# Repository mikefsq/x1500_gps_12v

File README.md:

# x1500_gps_12v

KiCad project for a daughterboard that powers a [Geekworm X1500](https://geekworm.com/products/x1500) (Raspberry Pi CM5,
1GbE, Dual M.2 NVMe SSD). It powers the Pi from 12V and adds a NEO-M9N GPS receiver 
with PPS, an SHT45 humidity sensor and a BMP581 pressure sensor. Also has a u.fl to SMA
jumper to help with attaching a WiFi Antenna.

Note this PCB does not cover the CM5 and its heat sink. If using another Pi board 
remember that it does not stack like a regular pi-hat.

## Driver software

The [Go GPS/weather library and diagnostic tools](driver/README.md) are in
`driver/`. They run on the Raspberry Pi and are licensed under AGPL-3.0-only.

## Raspberry Pi setup

```sh
sudo apt install gpsd gpsd-clients chrony pps-tools i2c-tools
```

Add to `/boot/firmware/config.txt`:

```
[all]
dtparam=i2c_arm=on
dtparam=uart0=on
dtoverlay=pps-gpio,gpiopin=18
usb_max_current_enable=1
dtparam=pciex1
```

Add to `/etc/default/gpsd`:

```
DEVICES="/dev/ttyAMA0"
GPSD_OPTIONS="-n -s 38400"
USBAUTO="false"
```

Add to `/etc/chrony/conf.d/gps.conf`:

```
refclock SHM 0 refid NMEA offset 0.0 precision 1e-1 noselect
refclock PPS /dev/pps0 refid PPS lock NMEA precision 1e-7 prefer
allow 192.168.0.0/24
```

Add to `/etc/systemd/system/gpsd.socket.d/90-network.conf`:

```
[Socket]
ListenStream=
ListenStream=/run/gpsd.sock
ListenStream=0.0.0.0:2947
```

Enable I2C `/etc/modules-load.d/i2c.conf`:

```
i2c-dev
```

```sh
sudo systemctl daemon-reload
sudo systemctl enable gpsd.socket
sudo reboot
```

`chronyc sources -v` shows PPS selected once the receiver has a fix.

## License

Hardware: [CERN-OHL-S-2.0](LICENSE).

Driver software: [AGPL-3.0-only](driver/LICENSE).

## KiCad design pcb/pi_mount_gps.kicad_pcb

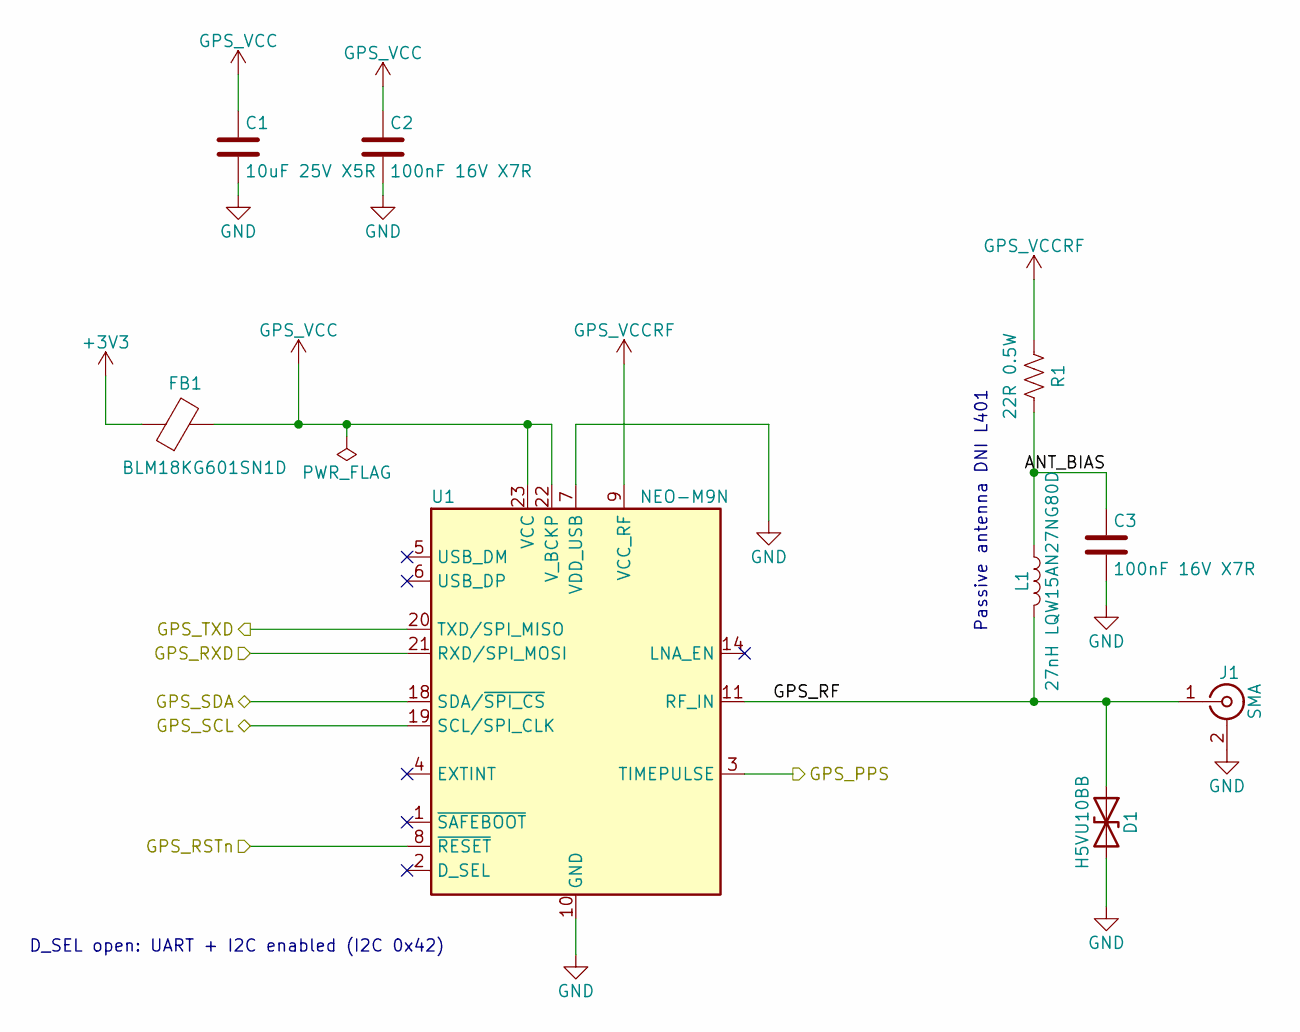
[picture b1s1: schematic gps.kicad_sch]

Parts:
C1: 10uF 25V X5R; C_0805_2012Metric; LCSC C15850
C2, C3: 100nF 16V X7R; C_0402_1005Metric; LCSC C1525
D1: H5VU10BB; D_0402_1005Metric; LCSC C20615786
FB1: BLM18KG601SN1D; L_0603_1608Metric; LCSC C85833
J1: SMA; SMA_Molex_73251-1153_EdgeMount_Horizontal
L1: 27nH LQW15AN27NG80D; L_0402_1005Metric; LCSC C882469
R1: 22R 0.5W; R_1206_3216Metric; LCSC C2845146
U1: NEO-M9N; ublox_NEO; LCSC C5119087

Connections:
+3V3: FB1.1; also elsewhere on the board
/GPS/ANT_BIAS: C3.1, L1.1, R1.2
/GPS/GPS_RF: D1.1 (A1), J1.1 (In), L1.2, U1.11 (RF_IN)
/GPS_PPS: U1.3 (TIMEPULSE); also elsewhere on the board
/GPS_RSTn: U1.8 (~RESET); also elsewhere on the board
/GPS_RXD: U1.21 (RXD/SPI_MOSI); also elsewhere on the board
/GPS_TXD: U1.20 (TXD/SPI_MISO); also elsewhere on the board
/I2C1_SCL: U1.19 (SCL/SPI_CLK); also elsewhere on the board
/I2C1_SDA: U1.18 (SDA/~SPI_CS); also elsewhere on the board
GND: C1.2, C2.2, C3.2, D1.2 (A2), J1.2 (Ext), U1.7 (VDD_USB), U1.10 (GND), U1.12 (GND), U1.13 (GND), U1.24 (GND); also elsewhere on the board
GPS_VCC: C1.1, C2.1, FB1.2, U1.22 (V_BCKP), U1.23 (VCC)
GPS_VCCRF: R1.1, U1.9 (VCC_RF)

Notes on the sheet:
D_SEL open: UART + I2C enabled (I2C 0x42)
Passive antenna DNI L401

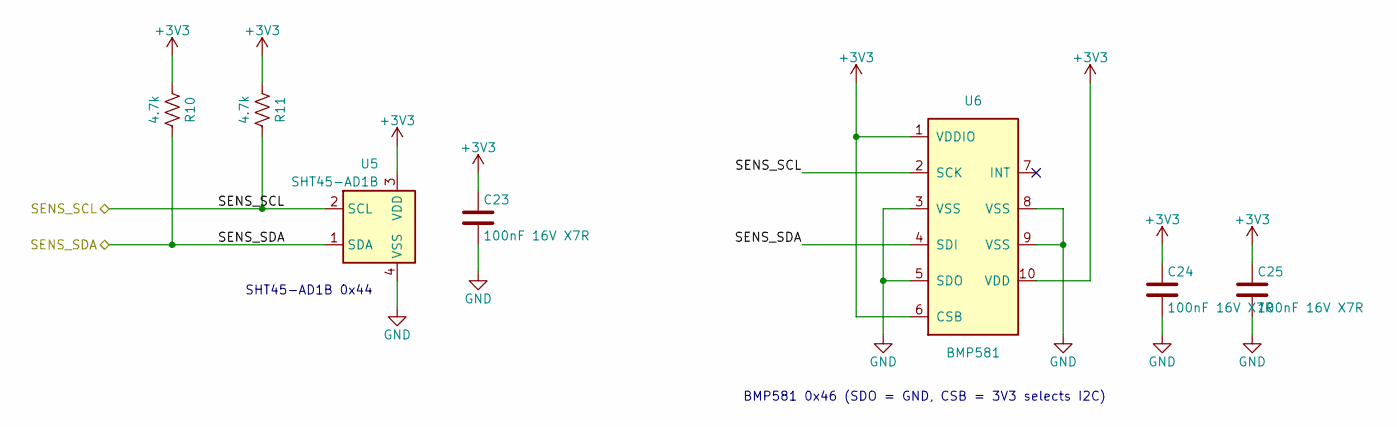
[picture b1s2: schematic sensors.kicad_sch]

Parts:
C23, C24, C25: 100nF 16V X7R; C_0402_1005Metric; LCSC C1525
R10, R11: 4.7k; R_0402_1005Metric; LCSC C25900
U5: SHT45-AD1B; Sensirion_DFN-4_1.5x1.5mm_P0.8mm_SHT4x_NoCentralPad; LCSC C5221601
U6: BMP581; Bosch_LGA-10_2x2mm_P0.5mm_BMP581; LCSC C5362283

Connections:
+3V3: C23.1, C24.1, C25.1, R10.1, R11.1, U5.3 (VDD), U6.1 (VDDIO), U6.6 (CSB), U6.10 (VDD); also elsewhere on the board
/I2C1_SCL: R11.2, U5.2 (SCL), U6.2 (SCK); also elsewhere on the board
/I2C1_SDA: R10.2, U5.1 (SDA), U6.4 (SDI); also elsewhere on the board
GND: C23.2, C24.2, C25.2, U5.4 (VSS), U6.3 (VSS), U6.5 (SDO), U6.8 (VSS), U6.9 (VSS); also elsewhere on the board

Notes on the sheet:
BMP581 0x46 (SDO = GND, CSB = 3V3 selects I2C)
SHT45-AD1B 0x44

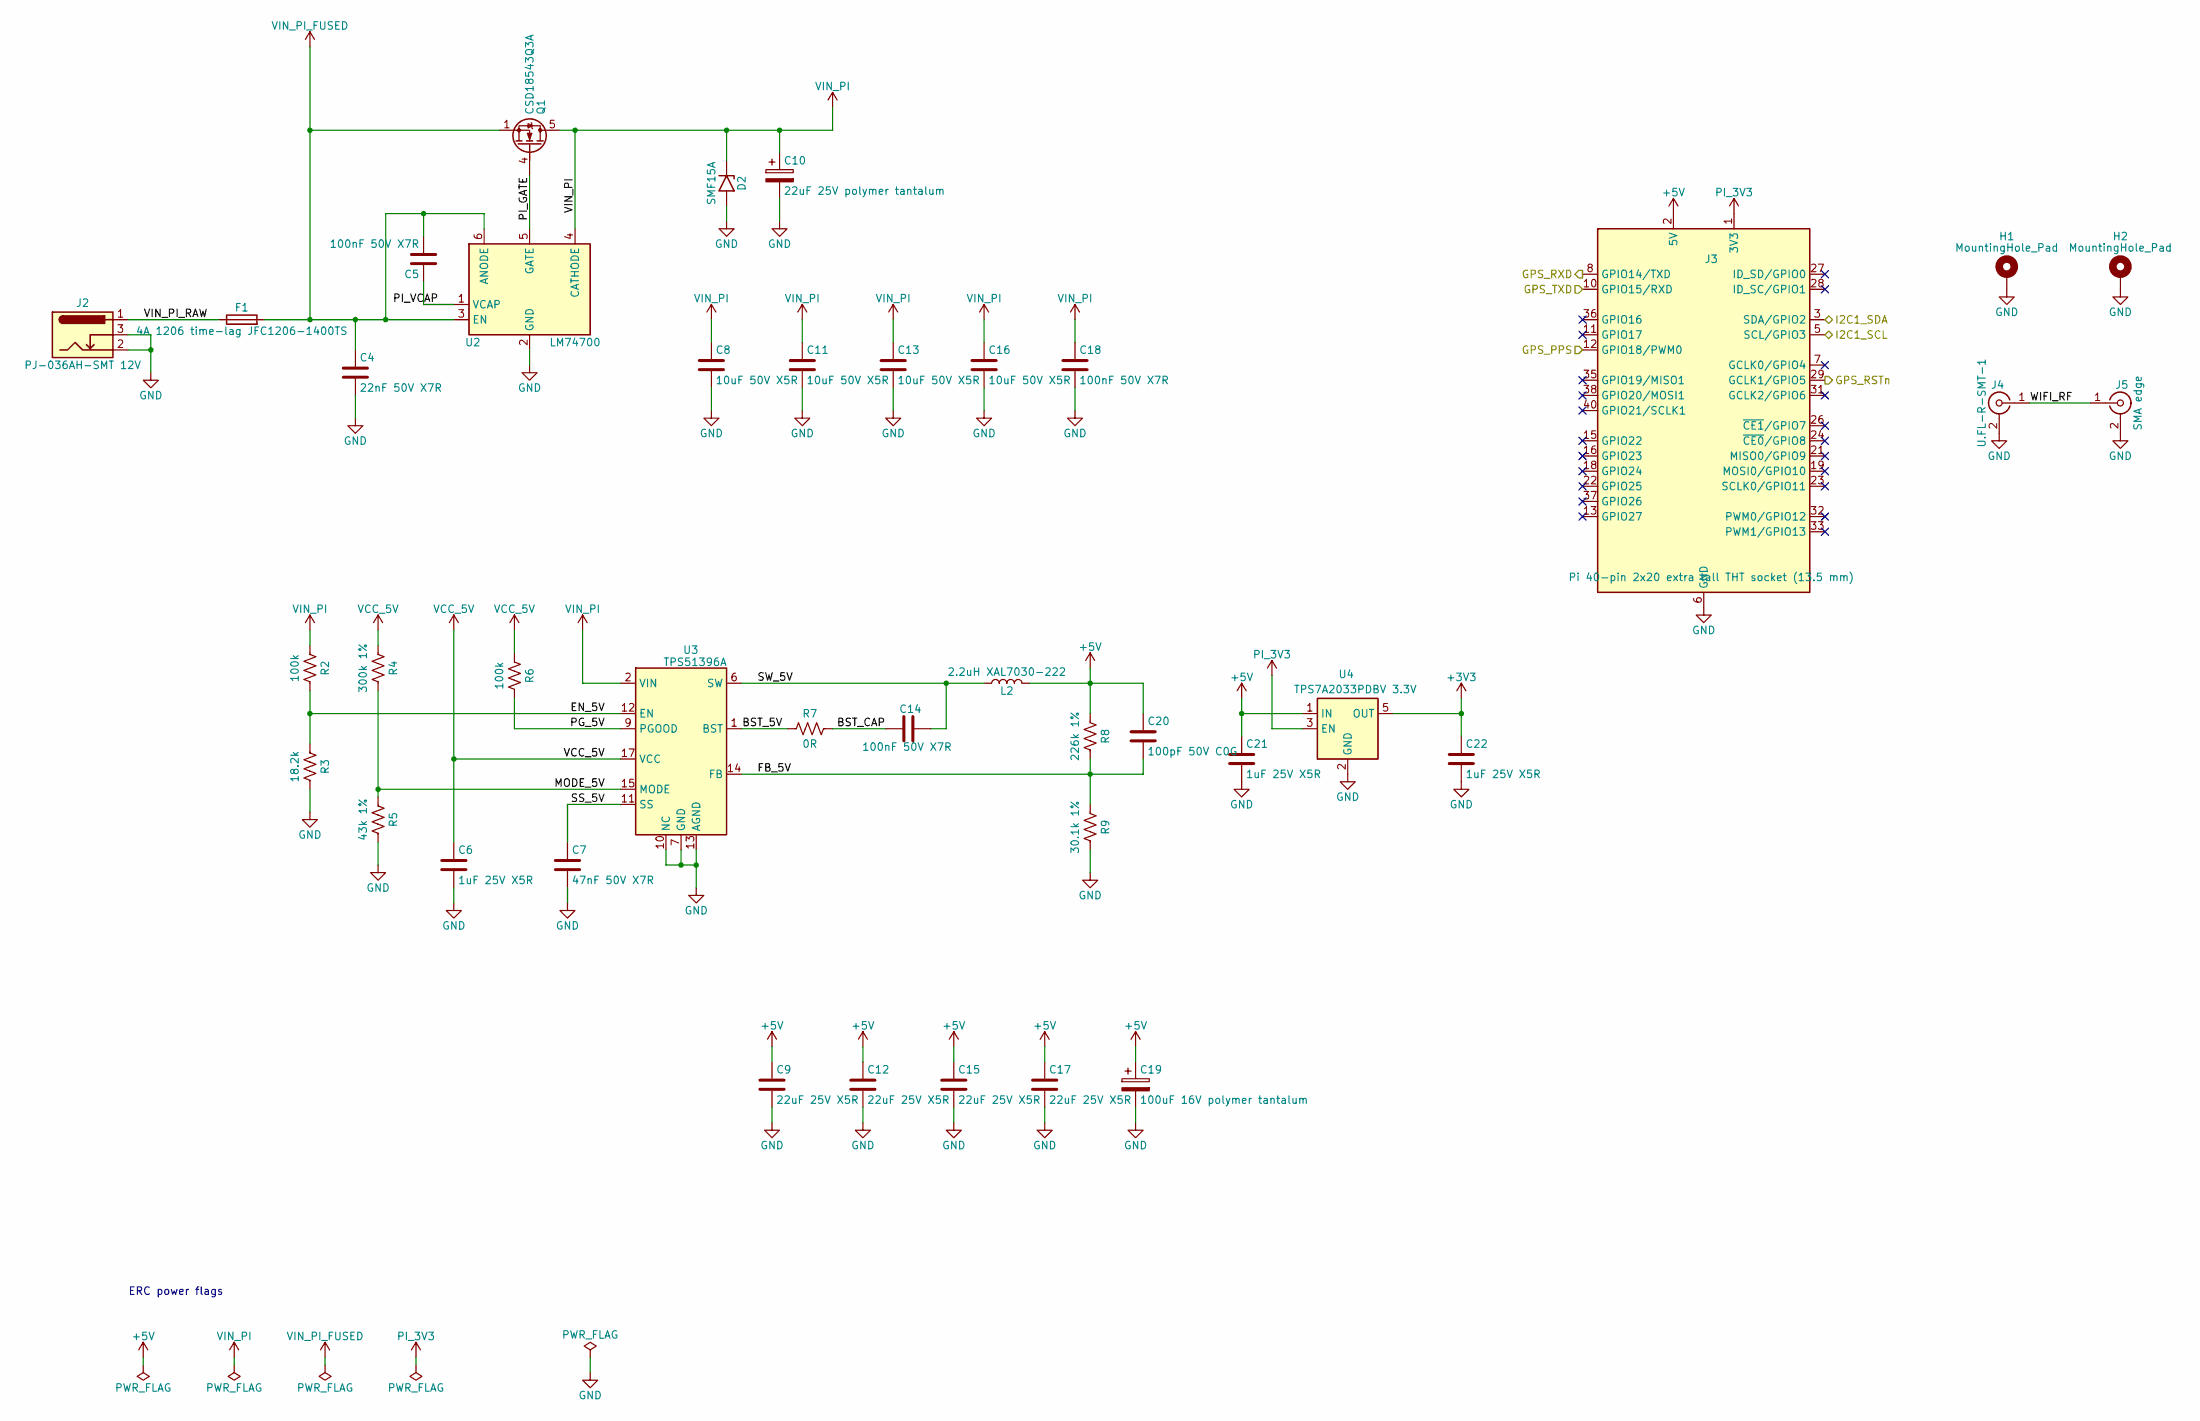
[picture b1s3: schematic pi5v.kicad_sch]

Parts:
C4: 22nF 50V X7R; C_0402_1005Metric; LCSC C1532
C5, C14, C18: 100nF 50V X7R; C_0402_1005Metric; LCSC C307331
C6, C21, C22: 1uF 25V X5R; C_0402_1005Metric; LCSC C52923
C7: 47nF 50V X7R; C_0402_1005Metric; LCSC C880605
C8, C11, C13, C16: 10uF 50V X5R; C_0805_2012Metric; LCSC C440198
C9, C12, C15, C17: 22uF 25V X5R; C_1206_3216Metric; LCSC C12891
C10: 22uF 25V polymer tantalum; CP_EIA-3528-21_Kemet-B; LCSC C696813
C19: 100uF 16V polymer tantalum; CP_EIA-7343-31_Kemet-D; LCSC C212713
C20: 100pF 50V C0G; C_0402_1005Metric; LCSC C1546
D2: SMF15A; D_SOD-123F; LCSC C19077509
F1: 4A 1206 time-lag JFC1206-1400TS; Fuse_1206_3216Metric; LCSC C52204055
H1, H2: MountingHole_Pad; MountingHole_2.7mm_M2.5_Pad_Via
J2: PJ-036AH-SMT 12V; BarrelJack_SameSky_PJ-036AH-SMT_Horizontal
J3: Pi 40-pin 2x20 extra tall THT socket (13.5 mm); PinSocket_2x20_P2.54mm_Vertical
J4: U.FL-R-SMT-1; U.FL_Hirose_U.FL-R-SMT-1_Vertical; LCSC C88374
J5: SMA edge; SMA_Molex_73251-1153_EdgeMount_Horizontal
L2: 2.2uH XAL7030-222; L_Coilcraft_XAL7030-222; LCSC C19191686
Q1: CSD18543Q3A; VSON-8_3.3x3.3mm_P0.65mm_NexFET; LCSC C840100
R2, R6: 100k; R_0402_1005Metric; LCSC C25741
R3: 18.2k; R_0402_1005Metric; LCSC C2998079
R4: 300k 1%; R_0402_1005Metric; LCSC C25774
R5: 43k 1%; R_0402_1005Metric; LCSC C54920674
R7: 0R; R_0402_1005Metric; LCSC C17168
R8: 226k 1%; R_0402_1005Metric; LCSC C5121518
R9: 30.1k 1%; R_0402_1005Metric; LCSC C2998131
U2: LM74700; SOT-23-6; LCSC C2653623
U3: TPS51396A; Texas_RJE0020A_VQFN-20-1EP_3x3mm_P0.45mm_EP0.675x0.76mm; LCSC C3032872
U4: TPS7A2033PDBV 3.3V; SOT-23-5; LCSC C2862740

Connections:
+3V3: C22.1, U4.5 (OUT); also elsewhere on the board
+5V: C9.1, C12.1, C15.1, C17.1, C19.1, C20.1, C21.1, J3.2 (5V), J3.4 (5V), L2.2, R8.1, U4.1 (IN)
/GPS_PPS: J3.12 (GPIO18/PWM0); also elsewhere on the board
/GPS_RSTn: J3.29 (GCLK1/GPIO5); also elsewhere on the board
/GPS_RXD: J3.8 (GPIO14/TXD); also elsewhere on the board
/GPS_TXD: J3.10 (GPIO15/RXD); also elsewhere on the board
/I2C1_SCL: J3.5 (SCL/GPIO3); also elsewhere on the board
/I2C1_SDA: J3.3 (SDA/GPIO2); also elsewhere on the board
/Pi 5V/BST_5V: R7.1, U3.1 (BST)
/Pi 5V/BST_CAP: C14.1, R7.2
/Pi 5V/EN_5V: R2.2, R3.1, U3.12 (EN)
/Pi 5V/FB_5V: C20.2, R8.2, R9.1, U3.14 (FB)
/Pi 5V/MODE_5V: R4.2, R5.1, U3.15 (MODE)
/Pi 5V/PG_5V: R6.2, U3.9 (PGOOD)
/Pi 5V/PI_GATE: Q1.4 (G), U2.5 (GATE)
/Pi 5V/PI_VCAP: C5.1, U2.1 (VCAP)
/Pi 5V/SS_5V: C7.1, U3.11 (SS)
/Pi 5V/SW_5V: C14.2, L2.1, U3.6 (SW), U3.19 (SW), U3.20 (SW)
/Pi 5V/VIN_PI_RAW: F1.1, J2.1
/Pi 5V/WIFI_RF: J4.1 (In), J5.1 (In)
GND: C4.2, C6.2, C7.2, C8.2, C9.2, C10.2, C11.2, C12.2, C13.2, C15.2, C16.2, C17.2, C18.2, C19.2, C21.2, C22.2, D2.2 (A2), H1.1 (1_1), H2.1 (1_1), J2.2, J2.3, J3.6 (GND), J3.9 (GND), J3.14 (GND), J3.20 (GND), J3.25 (GND), J3.30 (GND), J3.34 (GND), J3.39 (GND), J4.2 (Ext), J5.2 (Ext), R3.2, R5.2, R9.2, U2.2 (GND), U3.7 (GND), U3.8 (GND), U3.10 (NC), U3.13 (AGND), U3.16 (NC), U3.18 (GND), U3.21 (GND), U4.2 (GND); also elsewhere on the board
PI_3V3: J3.1 (3V3), J3.17 (3V3), U4.3 (EN)
VCC_5V: C6.1, R4.1, R6.1, U3.17 (VCC)
VIN_PI: C8.1, C10.1, C11.1, C13.1, C16.1, C18.1, D2.1 (A1), Q1.5 (D), R2.1, U2.4 (CATHODE), U3.2 (VIN), U3.3 (VIN), U3.4 (VIN), U3.5 (VIN)
VIN_PI_FUSED: C4.1, C5.2, F1.2, Q1.1 (S), Q1.2 (S), Q1.3 (S), U2.3 (EN), U2.6 (ANODE)

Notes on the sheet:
ERC power flags

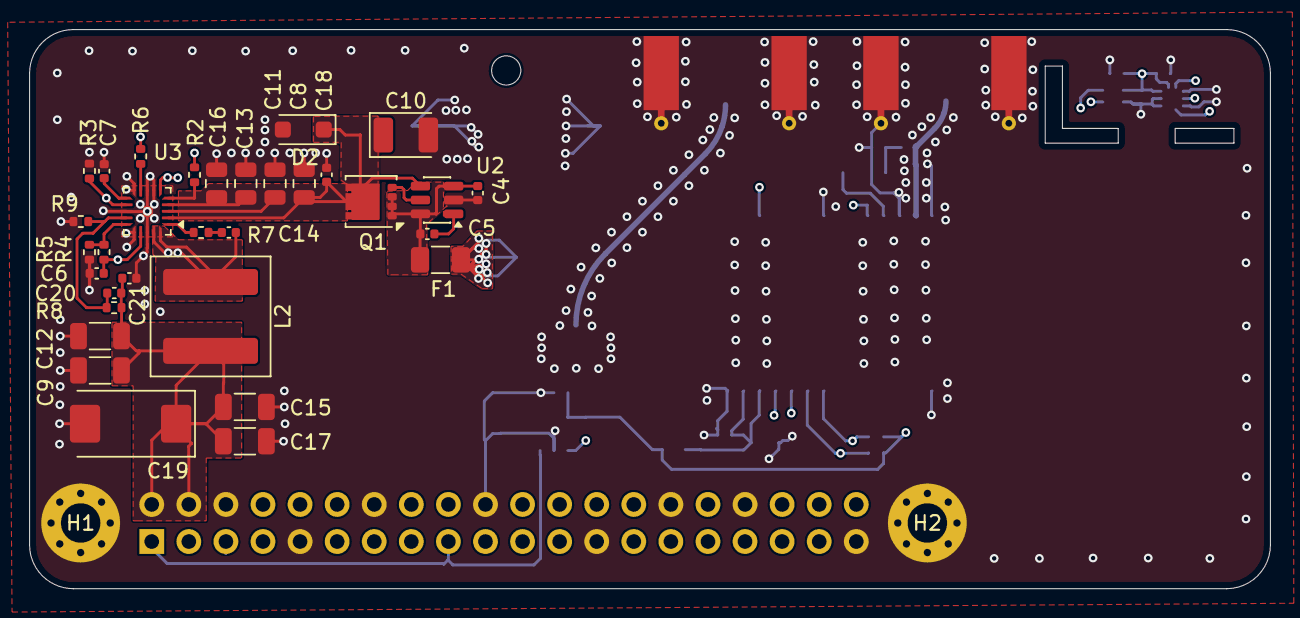
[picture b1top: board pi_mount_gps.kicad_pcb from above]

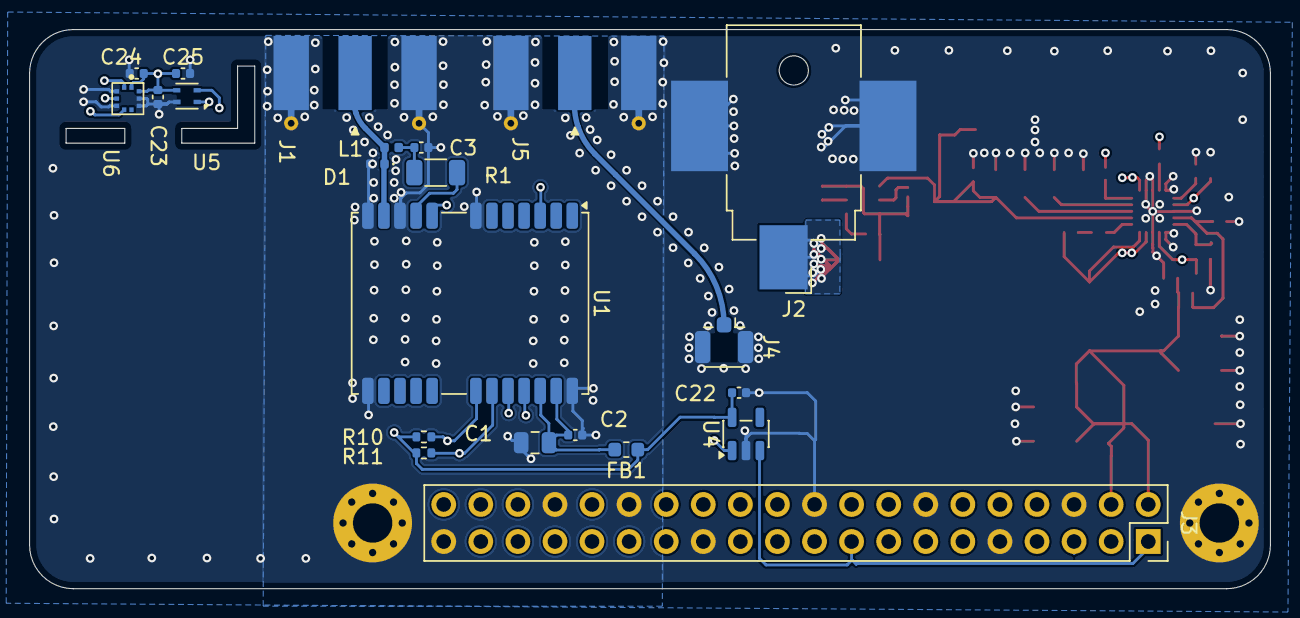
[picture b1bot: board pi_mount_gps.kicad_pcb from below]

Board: 4 copper layers, 85.0 x 38.3 mm, 56 parts (22 on the bottom side), 29 nets.
